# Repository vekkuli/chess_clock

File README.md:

# Chess Clock :clock1:

This repo contains design and fabrication files for my DIY chess clock project. The main components in the design are

    Two 4-digit red 7-segment displays
    MAX7219 display driver
    Pro Micro microcontroller board
    3D printed enclosure and other parts
    5 V power supply (e.g. PowerBoost 500C and LiPoly battery)
    Cut-to-shape acrylic window and tint film

## PCB

The KiCad project can be found in [chess_clock_pcb](chess_clock_pcb) folder. The [fabrication files](chess_clock_pcb/fabrication) are also included and can be used to order the PCBs directly. The fabrication files were produced according to JLCPCB requirements. Black solder mask is recommended.

All the components are through-hole. Happy soldering! Just don't make the same mistake I did the first time and forget which side each component is supposed to be on :grin:. See the correct placement here:

*Note that the SW2 JST connector is not actually required. I put it there just in case but the current FW does not use it.*

## 3D printed parts

I used black PLA and white PETG. The main body was printed the display/button side facing down and using organic supports (PrusaSlicer). The following mesh files can be found in the [3d_print folder](3d_print):

    3d_print/bottom.3mf
    3d_print/bushing.3mf
    3d_print/button_type1.3mf
    3d_print/button_type1_fill.3mf
    3d_print/button_type2.3mf
    3d_print/button_type2_fill.3mf
    3d_print/main_body.3mf
    3d_print/rocking_switch.3mf

*Note that I actually used off-the-shelf plastic bushings that I just happened to have around, but I imagine 3D printed ones will work just as well.*

## Acrylic window

The acrylic window cut shape can be found in [3d_print/acrylic_cut.dxf](3d_print/acrylic_cut.dxf). 2 mm acrylic can be easily cut using for example a CO2 laser cutter.

The 5 % tint film (e.g. car window tint) is needed to get good contrast from the display.

## Bill of materials

Full (I hope) bill of materials below. Most parts can be sourced from DigiKey.

| Quantity  | Item                          | Info/part number/digikey          |
|-----------|-------------------------------|-----------------------------------|
| 2         | 4-digit CC 7-segment display  | TDCR1060M-ND                      |
| 1         | Display driver                | MAX7219CNG-ND                     |
| 1         | USB-C port for 5 V input      | 2057-USB-C20-S-VT-CS15-WP-BK-ND   |
| 1         | 10k 1/4W resistor             | Affects LED brightness            |
| 1         | JST PH 2-pos connector        | B2B-PH-K-S                        |
| 1         | JST PH 3-pos connector        | B3B-PH-K-S                        |
| 1         | Arduino Pro Micro board       | Microcontroller board             |
| 4         | Tactile switches              | SW414-ND                          |
| 1         | Omron limit switch            | SS-5GL13                          |
| 1         | PowerBoost 500C               | 5V supply and LiPoly charger      |
| 1         | LiPoly battery                | e.g. 3.7 V/2500 mAh               |
| 1         | M2.5 screws and nuts          |                                   |
| 1         | M3 screws and nuts            |                                   |
| 1         | M4x40 socket head screw       | Cut to about 36 mm (or use M4x35) |
| 1         | M4 nyloc nut                  |                                   |
| 1         | Acrylic window (2 mm)         | Laser cut to shape                |
| 1         | 5 % dark tint film            | Greatly improves display contrast |
| 2         | (optional) O-ring             | To soften the button press        |

## Pro Micro brownout fix :exclamation:

I don't know how they managed to mess this up :angry: but Pro Micro has a design flaw that causes it to brown out when started by applying power directly via either USB or VCC pin, i.e., not using the regulator on the board. One way to fix this, and what I did, is to remove the regulator IC. While at it, I decided to remove the tantalum capacitors as well.

## Images

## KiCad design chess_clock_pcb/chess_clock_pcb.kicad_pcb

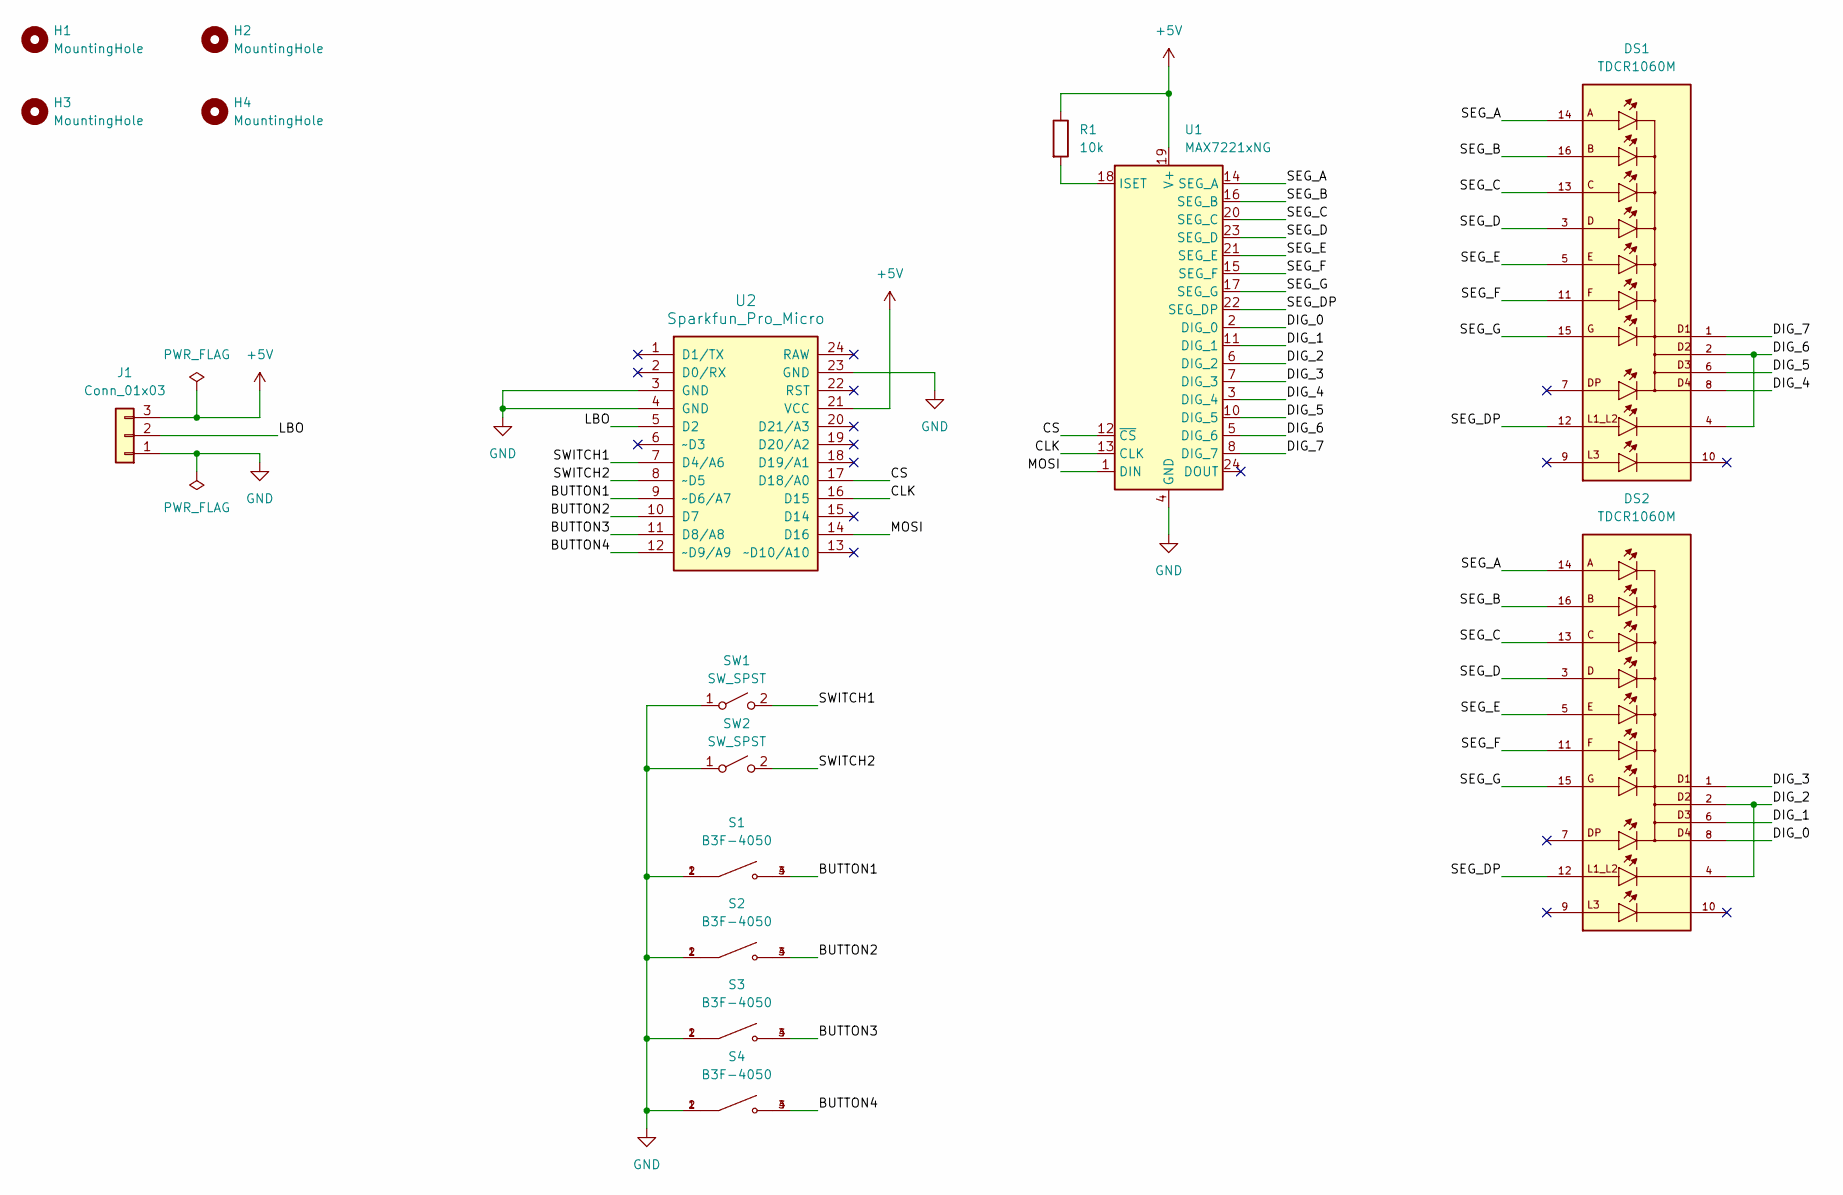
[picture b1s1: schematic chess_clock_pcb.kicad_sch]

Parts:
DS1, DS2: TDCR1060M; DISPLAY_TDCR1060M; PARTREV 1.7
H1, H2, H3, H4: MountingHole; MountingHole_3.2mm_M3
J1: Conn_01x03; JST_PH_B3B-PH-K_1x03_P2.00mm_Vertical
R1: 10k; R_Axial_DIN0207_L6.3mm_D2.5mm_P10.16mm_Horizontal
S1, S2, S3, S4: B3F-4050; SW_B3F-4050; Digi-Key_Part_Number SW414-ND
SW1, SW2: SW_SPST; JST_PH_B2B-PH-K_1x02_P2.00mm_Vertical
U1: MAX7221xNG; DIP-24_W7.62mm_LongPads
U2: Sparkfun_Pro_Micro

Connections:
+5V: J1.3, R1.1, U1.19 (V+), U2.21 (VCC)
/BUTTON1: S1.3, S1.4, U2.9 (~D6/A7)
/BUTTON2: S2.3, S2.4, U2.10 (D7)
/BUTTON3: S3.3, S3.4, U2.11 (D8/A8)
/BUTTON4: S4.3, S4.4, U2.12 (~D9/A9)
/CLK: U1.13 (CLK), U2.16 (D15)
/CS: U1.12 (~CS), U2.17 (D18/A0)
/DIG_0: DS2.8, U1.2 (DIG_0)
/DIG_1: DS2.6, U1.11 (DIG_1)
/DIG_2: DS2.2, DS2.4, U1.6 (DIG_2)
/DIG_3: DS2.1, U1.7 (DIG_3)
/DIG_4: DS1.8, U1.3 (DIG_4)
/DIG_5: DS1.6, U1.10 (DIG_5)
/DIG_6: DS1.2, DS1.4, U1.5 (DIG_6)
/DIG_7: DS1.1, U1.8 (DIG_7)
/LBO: J1.2, U2.5 (D2)
/MOSI: U1.1 (DIN), U2.14 (D16)
/SEG_A: DS1.14, DS2.14, U1.14 (SEG_A)
/SEG_B: DS1.16, DS2.16, U1.16 (SEG_B)
/SEG_C: DS1.13, DS2.13, U1.20 (SEG_C)
/SEG_D: DS1.3, DS2.3, U1.23 (SEG_D)
/SEG_DP: DS1.12, DS2.12, U1.22 (SEG_DP)
/SEG_E: DS1.5, DS2.5, U1.21 (SEG_E)
/SEG_F: DS1.11, DS2.11, U1.15 (SEG_F)
/SEG_G: DS1.15, DS2.15, U1.17 (SEG_G)
/SWITCH1: SW1.2 (B), U2.7 (D4/A6)
/SWITCH2: SW2.2 (B), U2.8 (~D5)
GND: J1.1, S1.1, S1.2, S2.1, S2.2, S3.1, S3.2, S4.1, S4.2, SW1.1 (A), SW2.1 (A), U1.4 (GND), U1.9 (GND), U2.3 (GND), U2.4 (GND), U2.23 (GND)
unnamed: R1.2, U1.18 (ISET)

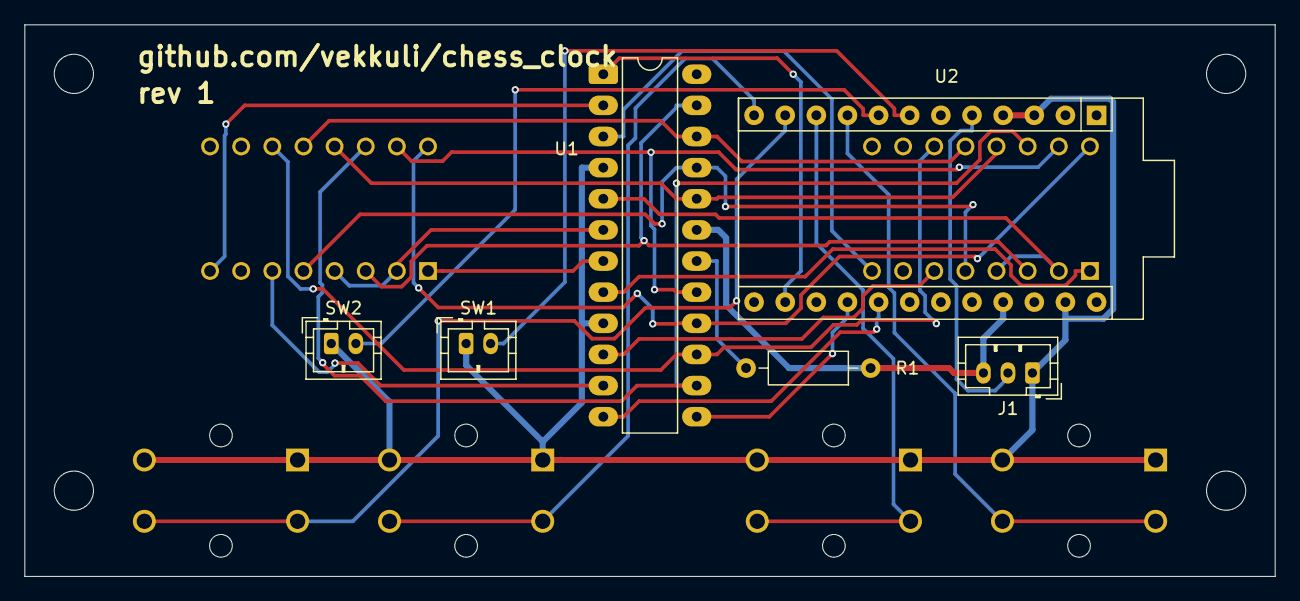
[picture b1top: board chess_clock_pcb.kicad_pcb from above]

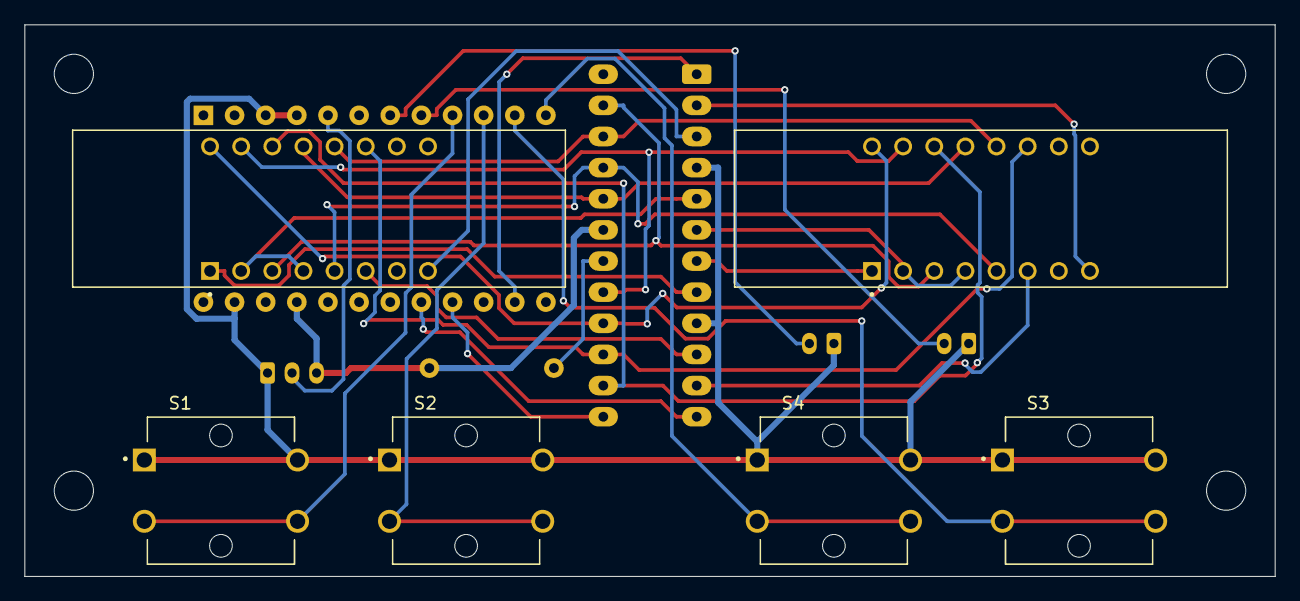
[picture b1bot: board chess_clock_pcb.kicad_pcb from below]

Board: 2 copper layers, 102.0 x 45.0 mm, 16 parts (6 on the bottom side), 29 nets.

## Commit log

2025-08-10 Committed public version of the repo.
2025-08-11 Added a GIF clip of the device in action and a photo
